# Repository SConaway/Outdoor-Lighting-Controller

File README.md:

# Outdoor-Lighting-Controller

## Description

This is the hardware (PCB) and the software (ESPHome configuration) for a Home Assistant-based motion-lights controller. ESPHome is used to interface with Home Assistant, which is responsible for controlling the lights and motion alerts, etc.

## Instructions

1. Download the board files from GitHub Release.
2. Order the needed parts ([parts list below](#parts-list)).
    1. I used [JLCPCB](jlcpcb.com) for the PCB; it cost me $2 (+ shipping) for 5 boards.
3. Assemble all parts on the PCB.
4. [Install ESPHome](https://esphome.io/guides/getting_started_command_line.html#getting-started-with-esphome).
5. Create the secrets file from the template.
6. Connect the ESP-01 to the programming adapter.
7. Run `esphome lights.yaml compile` to compile the firmware.
8. Run `esphome lights.yaml upload` to upload the newly-compiled firmware.
9. Place the ESP-01 in the PCB, paying attention to the direction of where it points

## Parts List

-   1x Custom designed Circuit Board
-   1x 8 channel Relay Board (any generic one will work as long as it supports the needed power for your lights)
-   1x MCP23017 I2C IO Expander (**IC1**)
-   1x ESP-01 module with programmer (**U1**)
-   1x [D24V10F3 Voltage Regulator](https://www.pololu.com/product/2830) (powers ESP-01) (**VR1**)
-   1x [D24V10F5 Voltage Regulator](https://www.pololu.com/product/2831) (powers the motion sensors and MCP23017) (**VR2**)
-   _up to_ 8x PIR motion sensor
-   _up to_ 8x lights and a way to power them
    -   I used 12 Volt DC LED lights and a 120VAC --> 12VDC power supply
-   jumper wires to connect the Relay Board to the PCB (either individual wires or a 1x10 cable works)
-   2x 1x10 male header (**RELAYS and J1**)
-   1x 2x4 female header (alternatively, 2 rows of 1x4 would work too) (**socket for ESP-01**)
-   1x 2-pin 3.5mm screw terminal blocks (**J2**)
-   1x 10-pin 2.54mm (0.1 in) screw terminal blocks (**PIRS**)
-   1x SPDT on/off switch (**S1**)
-   1x 10K ohm resistor (**R1**)
-   _optional_: 1x LED (**D1**) and 1x 330 ohm resistor (**R2**)
-   1x 5K ohm resistor (I used a 5.2K ohm resistor I had lying around) (**R3**)
-   1x safe casing that prevents access to 120VAC power
-   1x server running Home Assistant for automating the lights in reaction to the motion sensors

## Notes

-   If ESPHome is not working properly (either not installing or not compiling), you can upload the binary in the GitHub Release using another uploading tool, such as `esptool`.
-   I tested this with ESPHome v1.15.3.

## [Schematics](assets/Schematic.pdf)

## Credits

-   [ESPHome](esphome.io)
-   [Home Assistant](home-assistant.io)
-   [Sparkfun's EAGLE libraries](https://github.com/sparkfun/SparkFun-Eagle-Libraries)

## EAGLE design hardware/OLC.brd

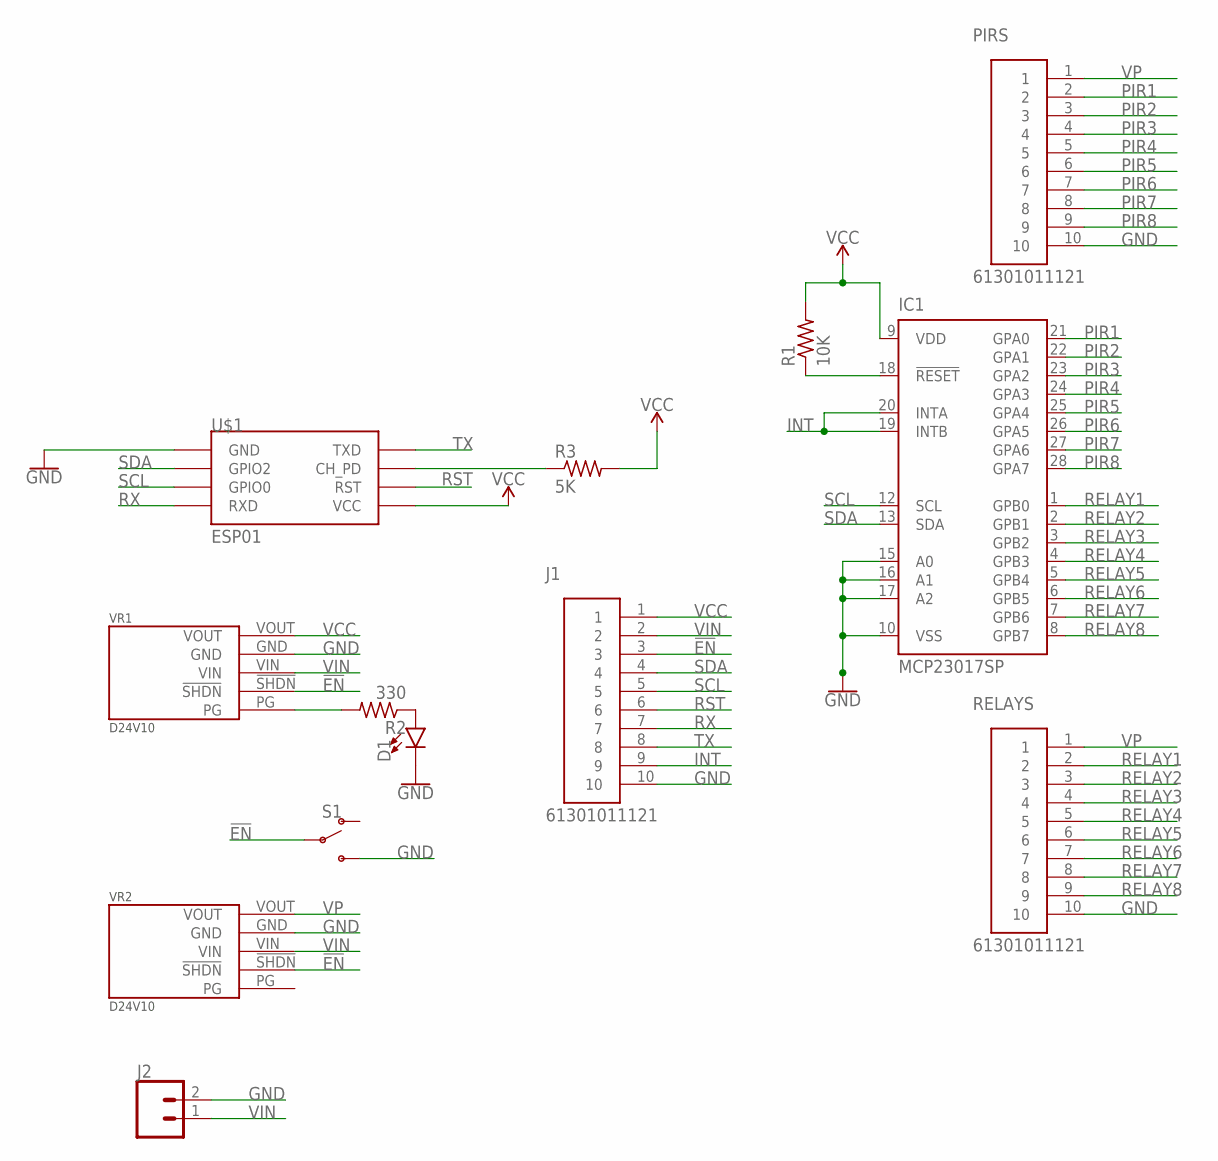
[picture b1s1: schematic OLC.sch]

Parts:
D1: LED5MM-KIT; LED_5MM-KIT
IC1: MCP23017SP; DIL28-3
J1: 61301011121
J2: CONN_023.5MM; SCREWTERMINAL-3.5MM-2
PIRS: 61301011121
R1: 10K; 0207/10
R2: 330; 0207/10
R3: 5K; 0207/10
RELAYS: 61301011121
S1: SWITCH-SPDT-PTH-11.6X4.0MM; SWITCH_SPDT_PTH_11.6X4.0MM
U$1: ESP01
VR1, VR2: D24V10

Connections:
!EN: J1.3, S1.2, VR1.!SHDN, VR2.!SHDN
GND: D1.K (C), IC1.10 (VSS), IC1.15 (A0), IC1.16 (A1), IC1.17 (A2), J1.10, J2.2, PIRS.10, RELAYS.10, S1.3 (S), U$1.GND, VR1.GND, VR2.GND
INT: IC1.19 (INTB), IC1.20 (INTA), J1.9
unnamed: IC1.18 (!RESET), R1.1
unnamed: D1.A, R2.1
unnamed: R2.2, VR1.PG
unnamed: R3.1, U$1.CH_PD
PIR1: IC1.21 (GPA0), PIRS.2
PIR2: IC1.22 (GPA1), PIRS.3
PIR3: IC1.23 (GPA2), PIRS.4
PIR4: IC1.24 (GPA3), PIRS.5
PIR5: IC1.25 (GPA4), PIRS.6
PIR6: IC1.26 (GPA5), PIRS.7
PIR7: IC1.27 (GPA6), PIRS.8
PIR8: IC1.28 (GPA7), PIRS.9
RELAY1: IC1.1 (GPB0), RELAYS.2
RELAY2: IC1.2 (GPB1), RELAYS.3
RELAY3: IC1.3 (GPB2), RELAYS.4
RELAY4: IC1.4 (GPB3), RELAYS.5
RELAY5: IC1.5 (GPB4), RELAYS.6
RELAY6: IC1.6 (GPB5), RELAYS.7
RELAY7: IC1.7 (GPB6), RELAYS.8
RELAY8: IC1.8 (GPB7), RELAYS.9
RST: J1.6, U$1.RST
RX: J1.7, U$1.RX (RXD)
SCL: IC1.12 (SCL), J1.5, U$1.GPIO0
SDA: IC1.13 (SDA), J1.4, U$1.GPIO2
TX: J1.8, U$1.TX (TXD)
VCC: IC1.9 (VDD), J1.1, R1.2, R3.2, U$1.VCC, VR1.VOUT
VIN: J1.2, J2.1, VR1.VIN, VR2.VIN
VP: PIRS.1, RELAYS.1, VR2.VOUT

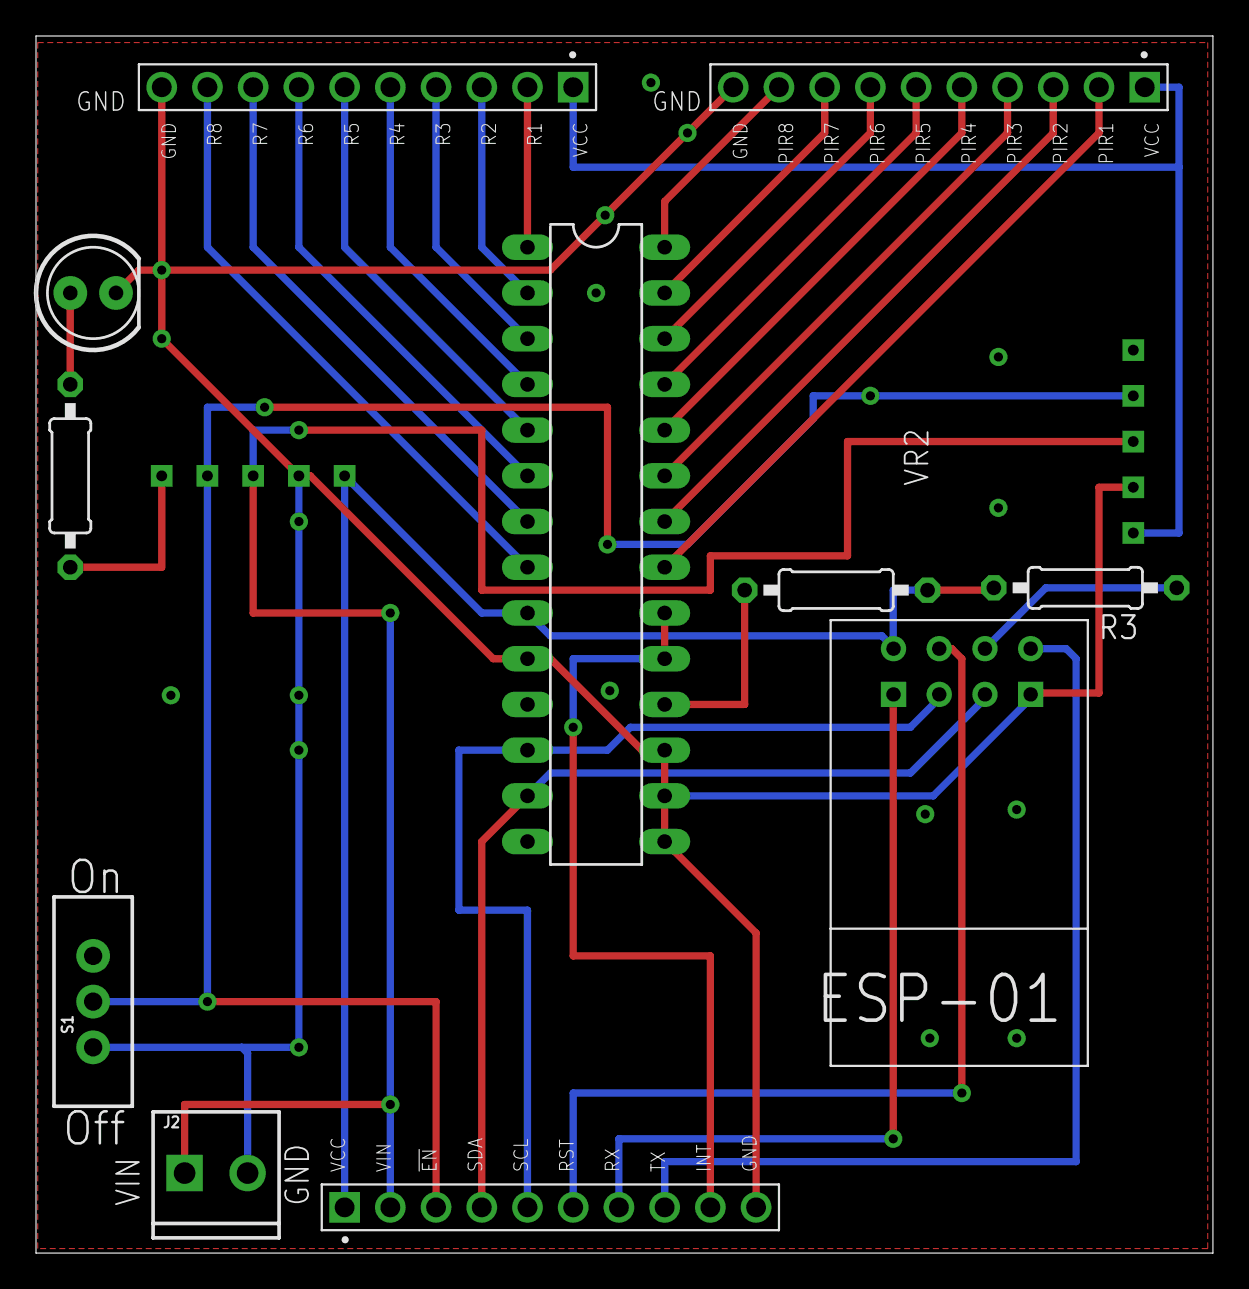
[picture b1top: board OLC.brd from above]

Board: 2 copper layers, 65.4 x 67.6 mm, 13 parts (0 on the bottom side), 31 nets.

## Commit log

2021-01-01 Inital Commit
2021-01-01 Add README.md
2021-01-01 Reorder Instructions slightly
2021-01-01 Add LICENSE
2021-01-01 Add coming soon notice to Instructions-PCB files
2021-01-01 basically useless changes from EAGLE
2021-01-01 Add Parts List and Schematic to README
2021-01-01 Add template secrets file
2021-01-01 Remove location-specific names from lights.yaml
    In newer Home Assistant versions, you can rename the entities there
2021-01-01 Add 5K ohm resistor to parts list
2021-01-01 Remove coming soon notice for binary
2021-01-01 Add 5K ohm resistor as R3
    The ESP01 needs a pull-up resistor on CH_PD to boot, and previous designs were missing it.
2021-01-01 Remove unneeded EAGLE files
2021-01-01 Edit template secrets file
2021-01-30 Add Render
2021-01-30 Rename schematic image
2021-01-30 Crop render image
2021-01-30 Crop #2?
2021-01-30 Add render image (#1)

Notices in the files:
parts and their libraries:
SparkFun-Switches: Licensing: Creative Commons ShareAlike 4.0 International - https://creativecommons.org/licenses/by-sa/4.0
